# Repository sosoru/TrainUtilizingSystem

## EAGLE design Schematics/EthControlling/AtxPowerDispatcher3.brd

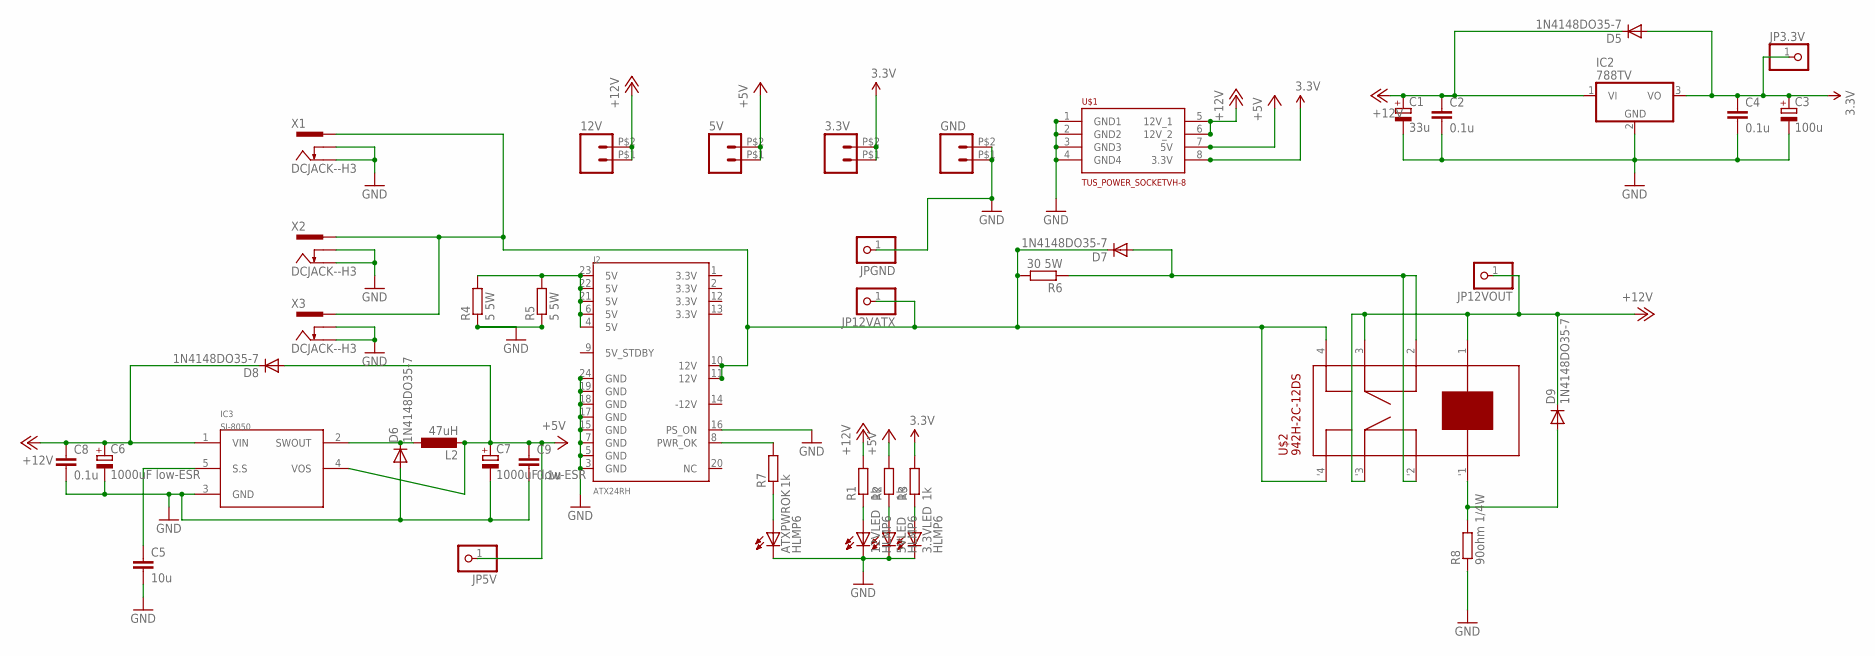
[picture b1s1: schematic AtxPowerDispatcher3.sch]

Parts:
3.3V, 5V, 12V: M02PTH2; 1X02_BIG
3.3VLED, 5VLED: HLMP6; MPN HLMP-6500
12VLED: HLMP6
ATXPWROK: HLMP6; MPN HLMP-6500
C1: 33u; E2,5-6E
C2, C4, C8, C9: 0.1u; C0603
C3: 100u; E2,5-6E
C5: 10u; C1206
C6, C7: 1000uF low-ESR; E2,5-6E
D5, D6, D7, D8, D9: 1N4148DO35-7; DO35-7
GND: M02PTH2; 1X02_BIG
IC2: 788TV; TO220V
IC3: SI-8050; TO220-5
J2: ATX24RH; ATX24_RIGHT_ANGLE
JP3.3V, JP5V, JP12VATX, JP12VOUT: PINHD-1X1; 1X01
JPGND: PINHD-1X1; 1X01
L2: 47uH; 2200-12.7
R1, R2, R3, R7: 1k; R0603
R4, R5: 5 5W; 0922/22
R6: 30 5W; 0922/22
R8: 90ohm 1/4W; 0207/10
U$1: TUS_POWER_SOCKETVH-8; VH_8
U$2: 942H-2C-12DS; 942H
X1, X2, X3: DCJACK--H3; 2DC-0005D100--H3

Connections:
3.3V: 3.3V.P$1 (1), 3.3V.P$2 (2), C3.+, C4.1, D5.A, IC2.3 (VO), JP3.3V.1, R3.2, U$1.8 (3.3V)
+5V: 5V.P$1 (1), 5V.P$2 (2), C7.+, C9.1, D8.A, IC3.4 (VOS), JP5V.1, L2.2, R2.2, U$1.7 (5V)
+12V: 12V.P$1 (1), 12V.P$2 (2), C1.+, C2.1, C6.+, C8.1, D5.C, D8.C, D9.C, IC2.1 (VI), IC3.1 (VIN), JP12VOUT.1, R1.2, U$1.5 (12V_1), U$1.6 (12V_2), U$2.1 (4), U$2.3 (2), U$2.'3 ('2)
GND: 3.3VLED.K, 5VLED.K, 12VLED.K, ATXPWROK.K, C1.-, C2.2, C3.-, C4.2, C5.2, C6.-, C7.-, C8.2, C9.2, D6.A, GND.P$1 (1), GND.P$2 (2), IC2.2 (GND), IC3.3 (GND), J2.3 (GND), J2.5 (GND), J2.7 (GND), J2.15 (GND), J2.16 (PS_ON), J2.17 (GND), J2.18 (GND), J2.19 (GND), J2.24 (GND), JPGND.1, R4.1, R5.1, R8.1, U$1.1 (GND1), U$1.2 (GND2), U$1.3 (GND3), U$1.4 (GND4), X1.2, X1.3, X2.2, X2.3, X3.2, X3.3
unnamed: 12VLED.A, R1.1
unnamed: J2.8 (PWR_OK), R7.2
unnamed: J2.4 (5V), J2.6 (5V), J2.21 (5V), J2.22 (5V), J2.23 (5V), R4.2, R5.2
unnamed: 5VLED.A, R2.1
unnamed: 3.3VLED.A, R3.1
unnamed: ATXPWROK.A, R7.1
unnamed: D9.A, R8.2, U$2.'1 ('4)
unnamed: D6.C, IC3.2 (SWOUT), L2.1
unnamed: D7.A, R6.1, U$2.2 (3), U$2.'2 ('3)
unnamed: D7.C, J2.10 (12V), J2.11 (12V), JP12VATX.1, R6.2, U$2.4 (1), U$2.'4 ('1), X1.1, X2.1, X3.1
unnamed: C5.1, IC3.5 (S.S)

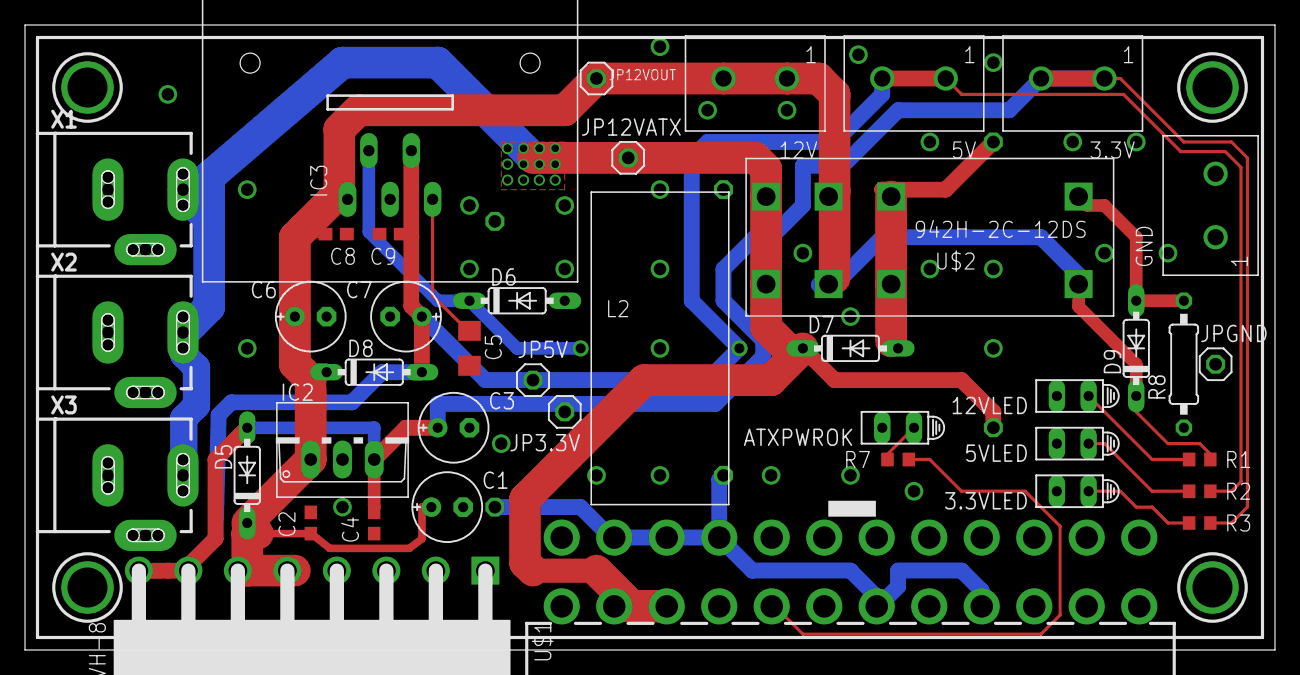
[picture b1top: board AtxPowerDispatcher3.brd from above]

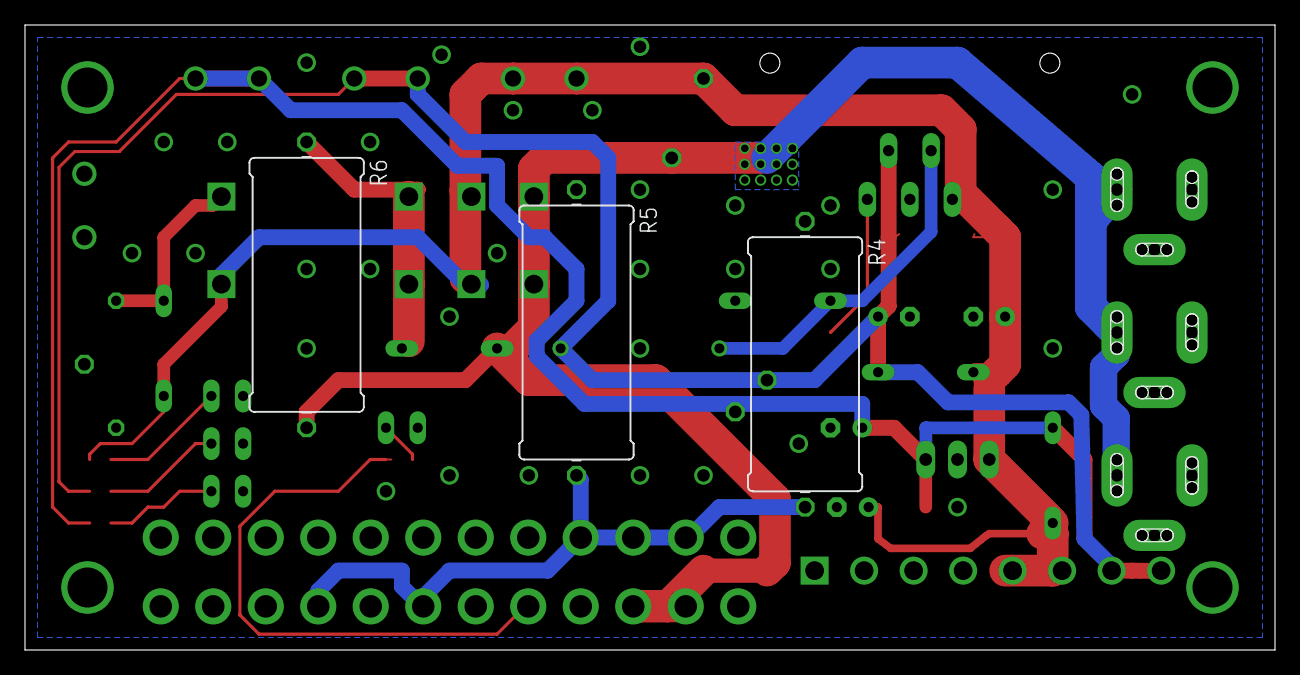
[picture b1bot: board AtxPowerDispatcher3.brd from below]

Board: 2 copper layers, 100.0 x 50.0 mm, 44 parts (3 on the bottom side), 15 nets.

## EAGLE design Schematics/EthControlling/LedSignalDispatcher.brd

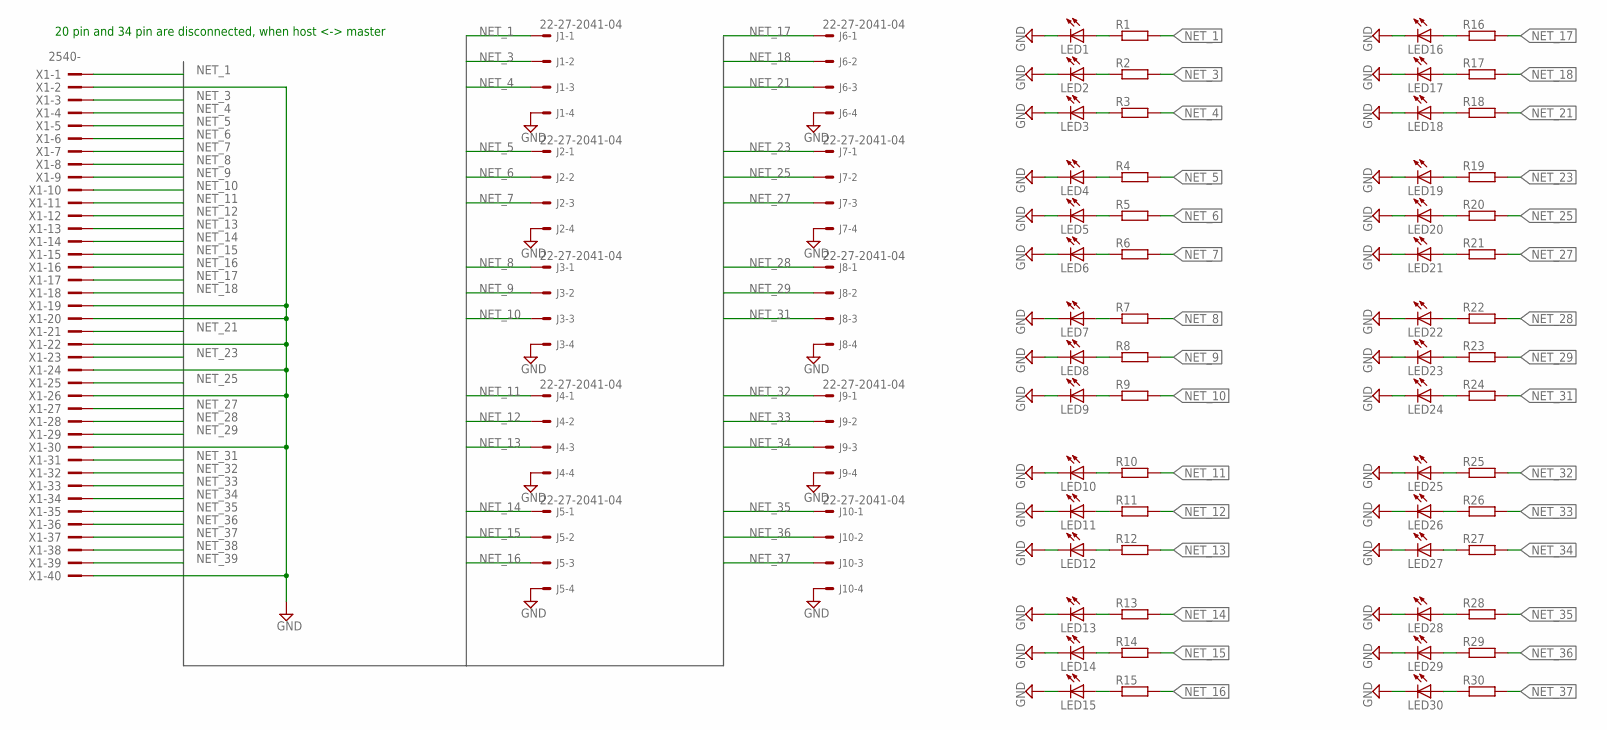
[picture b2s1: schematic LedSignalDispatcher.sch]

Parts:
J1, J2, J3, J4, J5, J6, J7, J8, J9, J10: 22-27-2041-04; 6410-04
LED1, LED2, LED3, LED4, LED5, LED6, LED7, LED8, LED9, LED10, LED11, LED12, LED13, LED14, LED15, LED16, LED17, LED18, LED19, LED20, LED21, LED22, LED23, LED24, LED25, LED26, LED27, LED28, LED29, LED30: LEDP-LCC-2; P-LCC-2
R1, R2, R3, R4, R5, R6, R7, R8, R9, R10, R11, R12, R13, R14, R15, R16, R17, R18, R19, R20, R21, R22, R23, R24, R25, R26, R27, R28, R29, R30: SMT-REF
X1: 2540-; PAK100/2500-40

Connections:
GND: J1.4, J2.4, J3.4, J4.4, J5.4, J6.4, J7.4, J8.4, J9.4, J10.4, LED1.C, LED2.C, LED3.C, LED4.C, LED5.C, LED6.C, LED7.C, LED8.C, LED9.C, LED10.C, LED11.C, LED12.C, LED13.C, LED14.C, LED15.C, LED16.C, LED17.C, LED18.C, LED19.C, LED20.C, LED21.C, LED22.C, LED23.C, LED24.C, LED25.C, LED26.C, LED27.C, LED28.C, LED29.C, LED30.C, X1.2, X1.19, X1.20, X1.22, X1.24, X1.26, X1.30, X1.40
unnamed: LED1.A, R1.2
unnamed: LED2.A, R2.2
unnamed: LED3.A, R3.2
unnamed: LED4.A, R4.2
unnamed: LED5.A, R5.2
unnamed: LED6.A, R6.2
unnamed: LED7.A, R7.2
unnamed: LED8.A, R8.2
unnamed: LED9.A, R9.2
unnamed: LED10.A, R10.2
unnamed: LED11.A, R11.2
unnamed: LED12.A, R12.2
unnamed: LED13.A, R13.2
unnamed: LED14.A, R14.2
unnamed: LED15.A, R15.2
unnamed: LED16.A, R16.2
unnamed: LED17.A, R17.2
unnamed: LED18.A, R18.2
unnamed: LED19.A, R19.2
unnamed: LED20.A, R20.2
unnamed: LED21.A, R21.2
unnamed: LED22.A, R22.2
unnamed: LED23.A, R23.2
unnamed: LED24.A, R24.2
unnamed: LED25.A, R25.2
unnamed: LED26.A, R26.2
unnamed: LED27.A, R27.2
unnamed: LED28.A, R28.2
unnamed: LED29.A, R29.2
unnamed: LED30.A, R30.2
NET_1: J1.1, R1.1, X1.1
NET_3: J1.2, R2.1, X1.3
NET_4: J1.3, R3.1, X1.4
NET_5: J2.1, R4.1, X1.5
NET_6: J2.2, R5.1, X1.6
NET_7: J2.3, R6.1, X1.7
NET_8: J3.1, R7.1, X1.8
NET_9: J3.2, R8.1, X1.9
NET_10: J3.3, R9.1, X1.10
NET_11: J4.1, R10.1, X1.11
NET_12: J4.2, R11.1, X1.12
NET_13: J4.3, R12.1, X1.13
NET_14: J5.1, R13.1, X1.14
NET_15: J5.2, R14.1, X1.15
NET_16: J5.3, R15.1, X1.16
NET_17: J6.1, R16.1, X1.17
NET_18: J6.2, R17.1, X1.18
NET_21: J6.3, R18.1, X1.21
NET_23: J7.1, R19.1, X1.23
NET_25: J7.2, R20.1, X1.25
NET_27: J7.3, R21.1, X1.27
NET_28: J8.1, R22.1, X1.28
NET_29: J8.2, R23.1, X1.29
NET_31: J8.3, R24.1, X1.31
NET_32: J9.1, R25.1, X1.32
NET_33: J9.2, R26.1, X1.33
NET_34: J9.3, R27.1, X1.34
NET_35: J10.1, R28.1, X1.35
NET_36: J10.2, R29.1, X1.36
NET_37: J10.3, R30.1, X1.37
NET_38: X1.38
NET_39: X1.39

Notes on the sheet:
20 pin and 34 pin are disconnected, when host <-> master

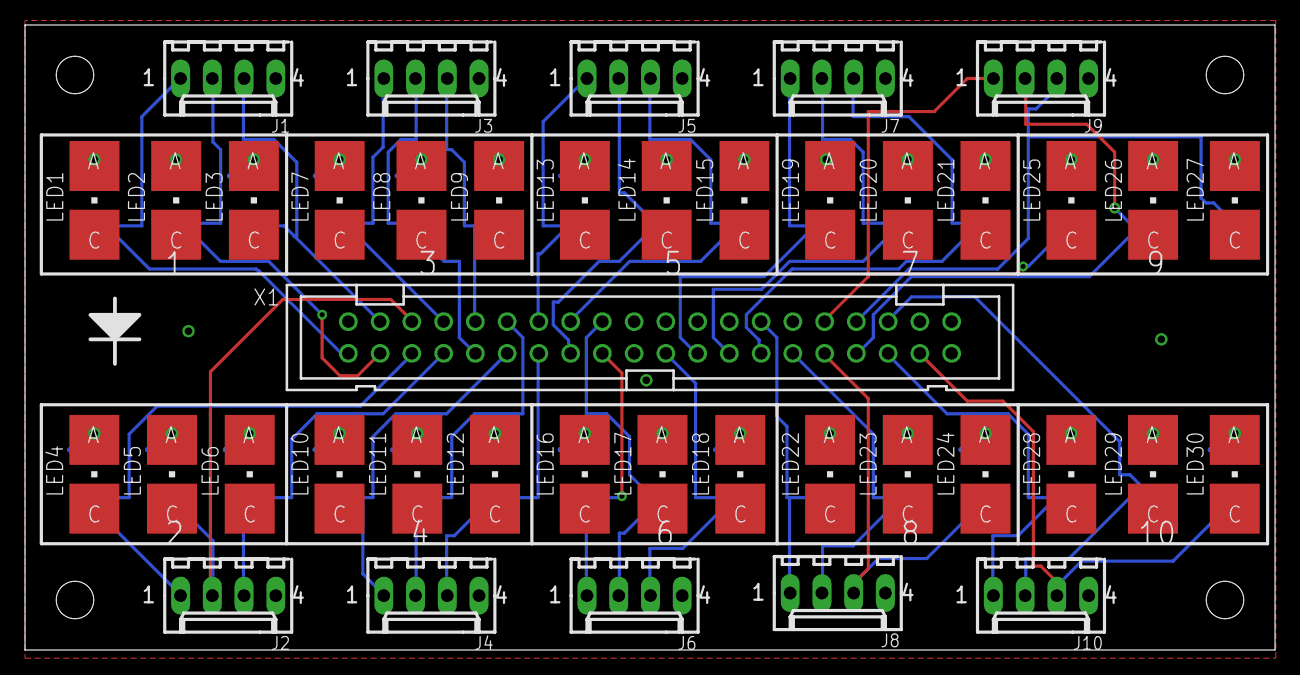
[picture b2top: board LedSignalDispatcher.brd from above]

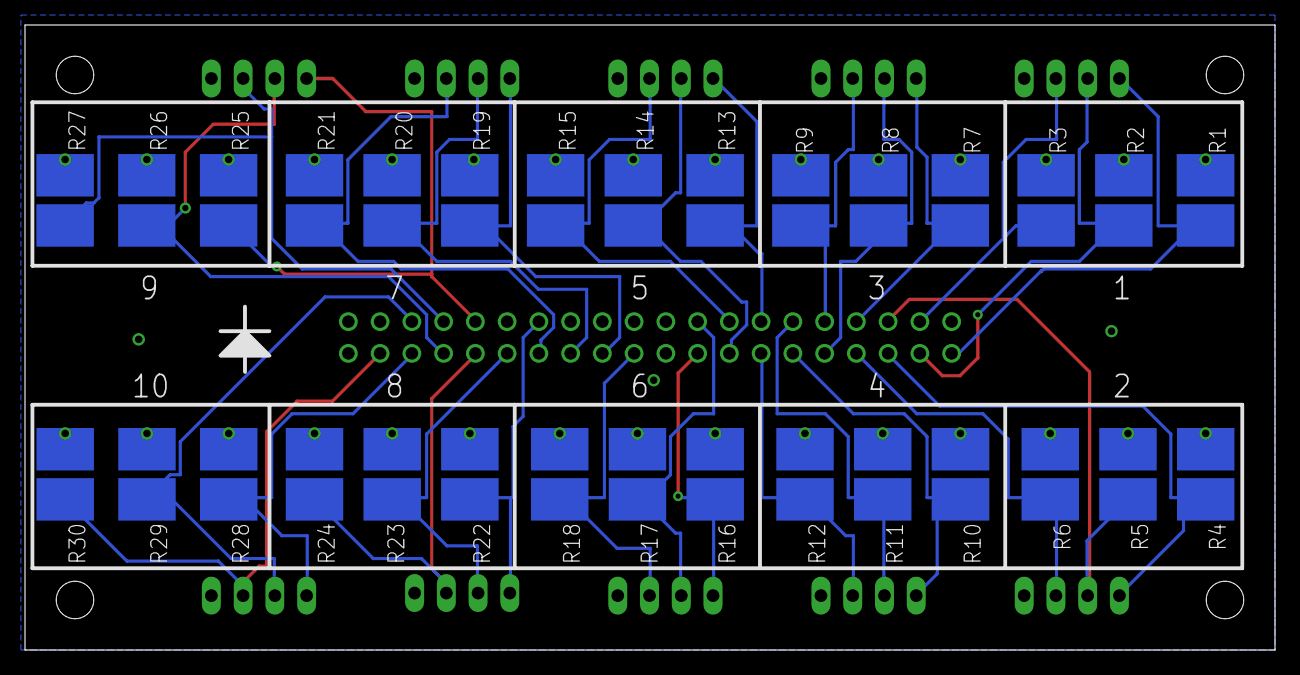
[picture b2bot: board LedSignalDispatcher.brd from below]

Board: 2 copper layers, 100.0 x 50.0 mm, 71 parts (30 on the bottom side), 61 nets.

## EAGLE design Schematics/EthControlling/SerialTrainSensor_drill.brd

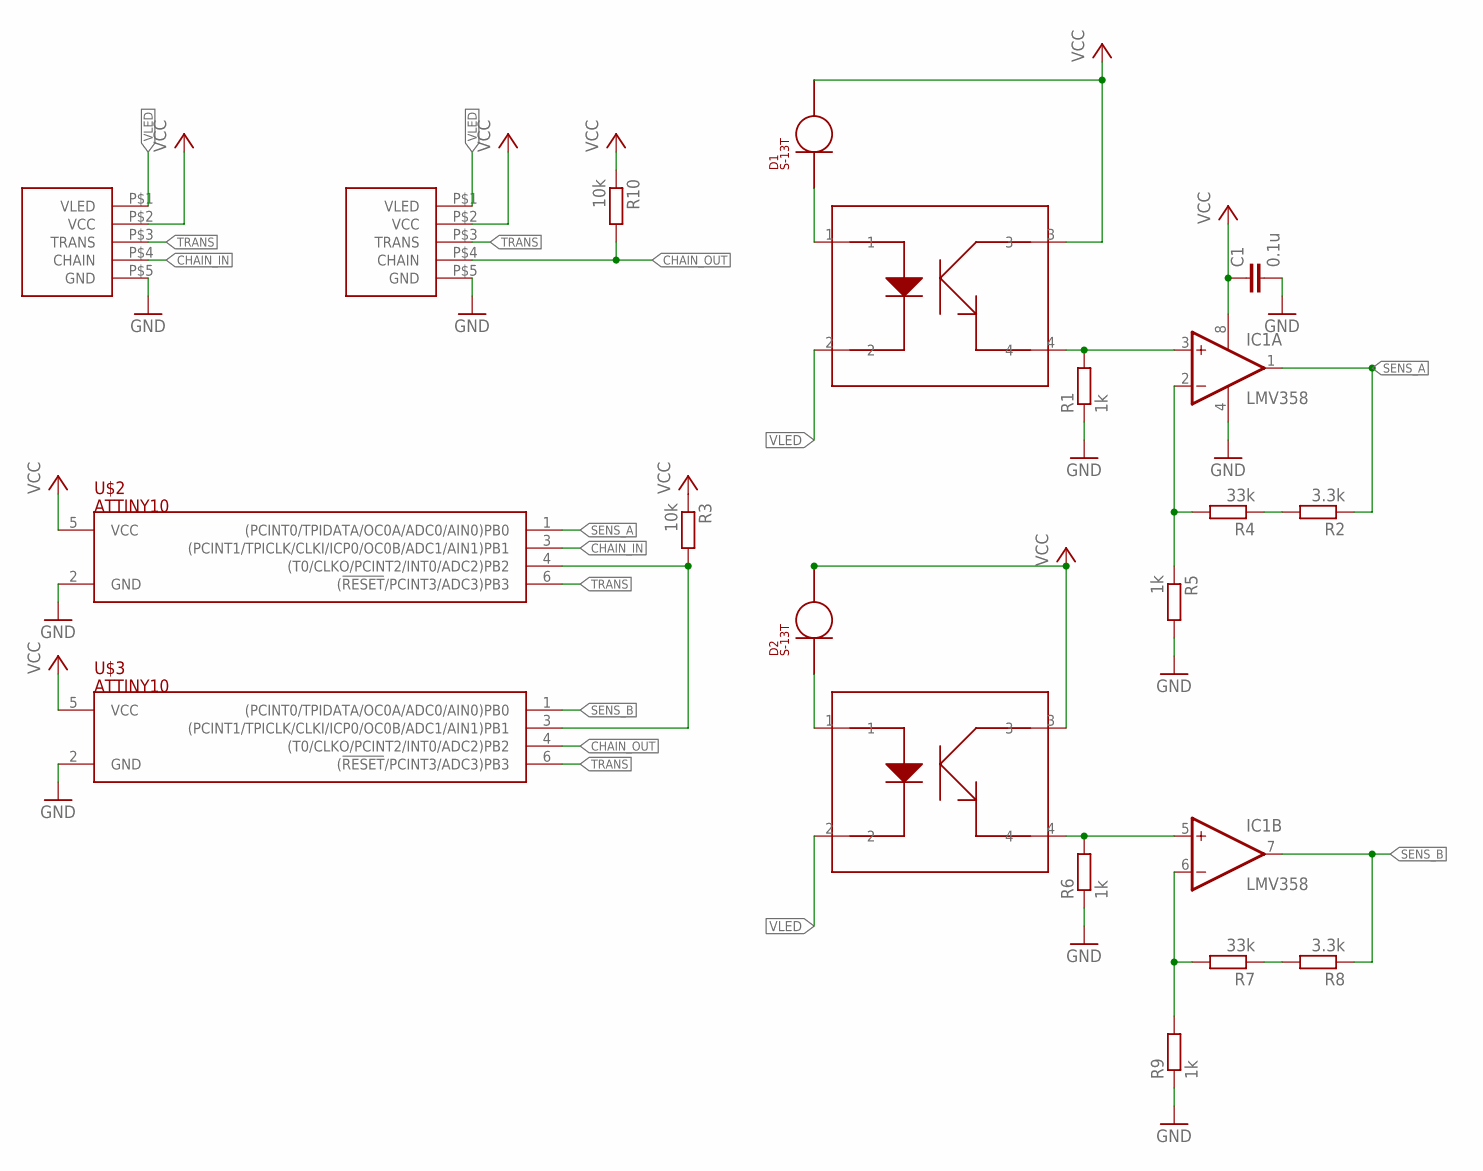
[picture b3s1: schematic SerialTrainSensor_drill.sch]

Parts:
C1: 0.1u; C0603
D1, D2: S-13T; S-1*3T
IC1: LMV358; TSSOP8
R1, R5, R6, R9: 1k; R0603
R2, R8: 3.3k; R0603
R3, R10: 10k; R0603
R4, R7: 33k; R0603
SMD1, SMD2: SERIAL_SENSORHALF; SERIAL_5_HALF
U$1, U$4: TPR-105F
U$2, U$3: ATTINY10; SOT-23

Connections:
CHAIN_IN: SMD1.P$4 (CHAIN), U$2.3 ((PCINT1/TPICLK/CLKI/ICP0/OC0B/ADC1/AIN1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)
CHAIN_OUT: R10.2, SMD2.P$4 (CHAIN), U$3.4 ((T0/CLKO/PCINT2/INT0/ADC2)PB2)
GND: C1.2, IC1.4 (V-), R1.1, R5.2, R6.1, R9.1, SMD1.P$5 (GND), SMD2.P$5 (GND), U$2.2 (GND), U$3.2 (GND)
unnamed: D1.C, U$1.1
unnamed: IC1.3 (+IN), R1.2, U$1.4
unnamed: D2.C, U$4.1
unnamed: R3.2, U$2.4 ((T0/CLKO/PCINT2/INT0/ADC2)PB2), U$3.3 ((PCINT1/TPICLK/CLKI/ICP0/OC0B/ADC1/AIN1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)
unnamed: IC1.5 (+IN), R6.2, U$4.4
unnamed: IC1.2 (-IN), R4.2, R5.1
unnamed: IC1.6 (-IN), R7.2, R9.2
unnamed: R2.2, R4.1
unnamed: R7.1, R8.2
SENS_A: IC1.1 (OUT), R2.1, U$2.1 ((PCINT0/TPIDATA/OC0A/ADC0/AIN0)PB0)
SENS_B: IC1.7 (OUT), R8.1, U$3.1 ((PCINT0/TPIDATA/OC0A/ADC0/AIN0)PB0)
TRANS: SMD1.P$3 (TRANS), SMD2.P$3 (TRANS), U$2.6 ((!RESET!/PCINT3/ADC3)PB3), U$3.6 ((!RESET!/PCINT3/ADC3)PB3)
VCC: C1.1, D1.A, D2.A, IC1.8 (V+), R3.1, R10.1, SMD1.P$2 (VCC), SMD2.P$2 (VCC), U$1.3, U$2.5 (VCC), U$3.5 (VCC), U$4.3
VLED: SMD1.P$1 (VLED), SMD2.P$1 (VLED), U$1.2, U$4.2

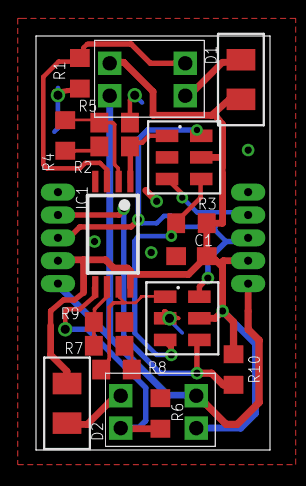
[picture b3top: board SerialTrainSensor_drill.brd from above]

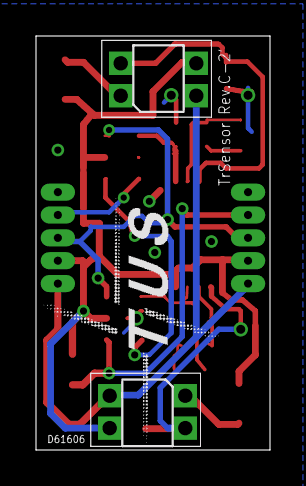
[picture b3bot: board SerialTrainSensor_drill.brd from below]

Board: 2 copper layers, 13.0 x 23.0 mm, 20 parts (2 on the bottom side), 17 nets.

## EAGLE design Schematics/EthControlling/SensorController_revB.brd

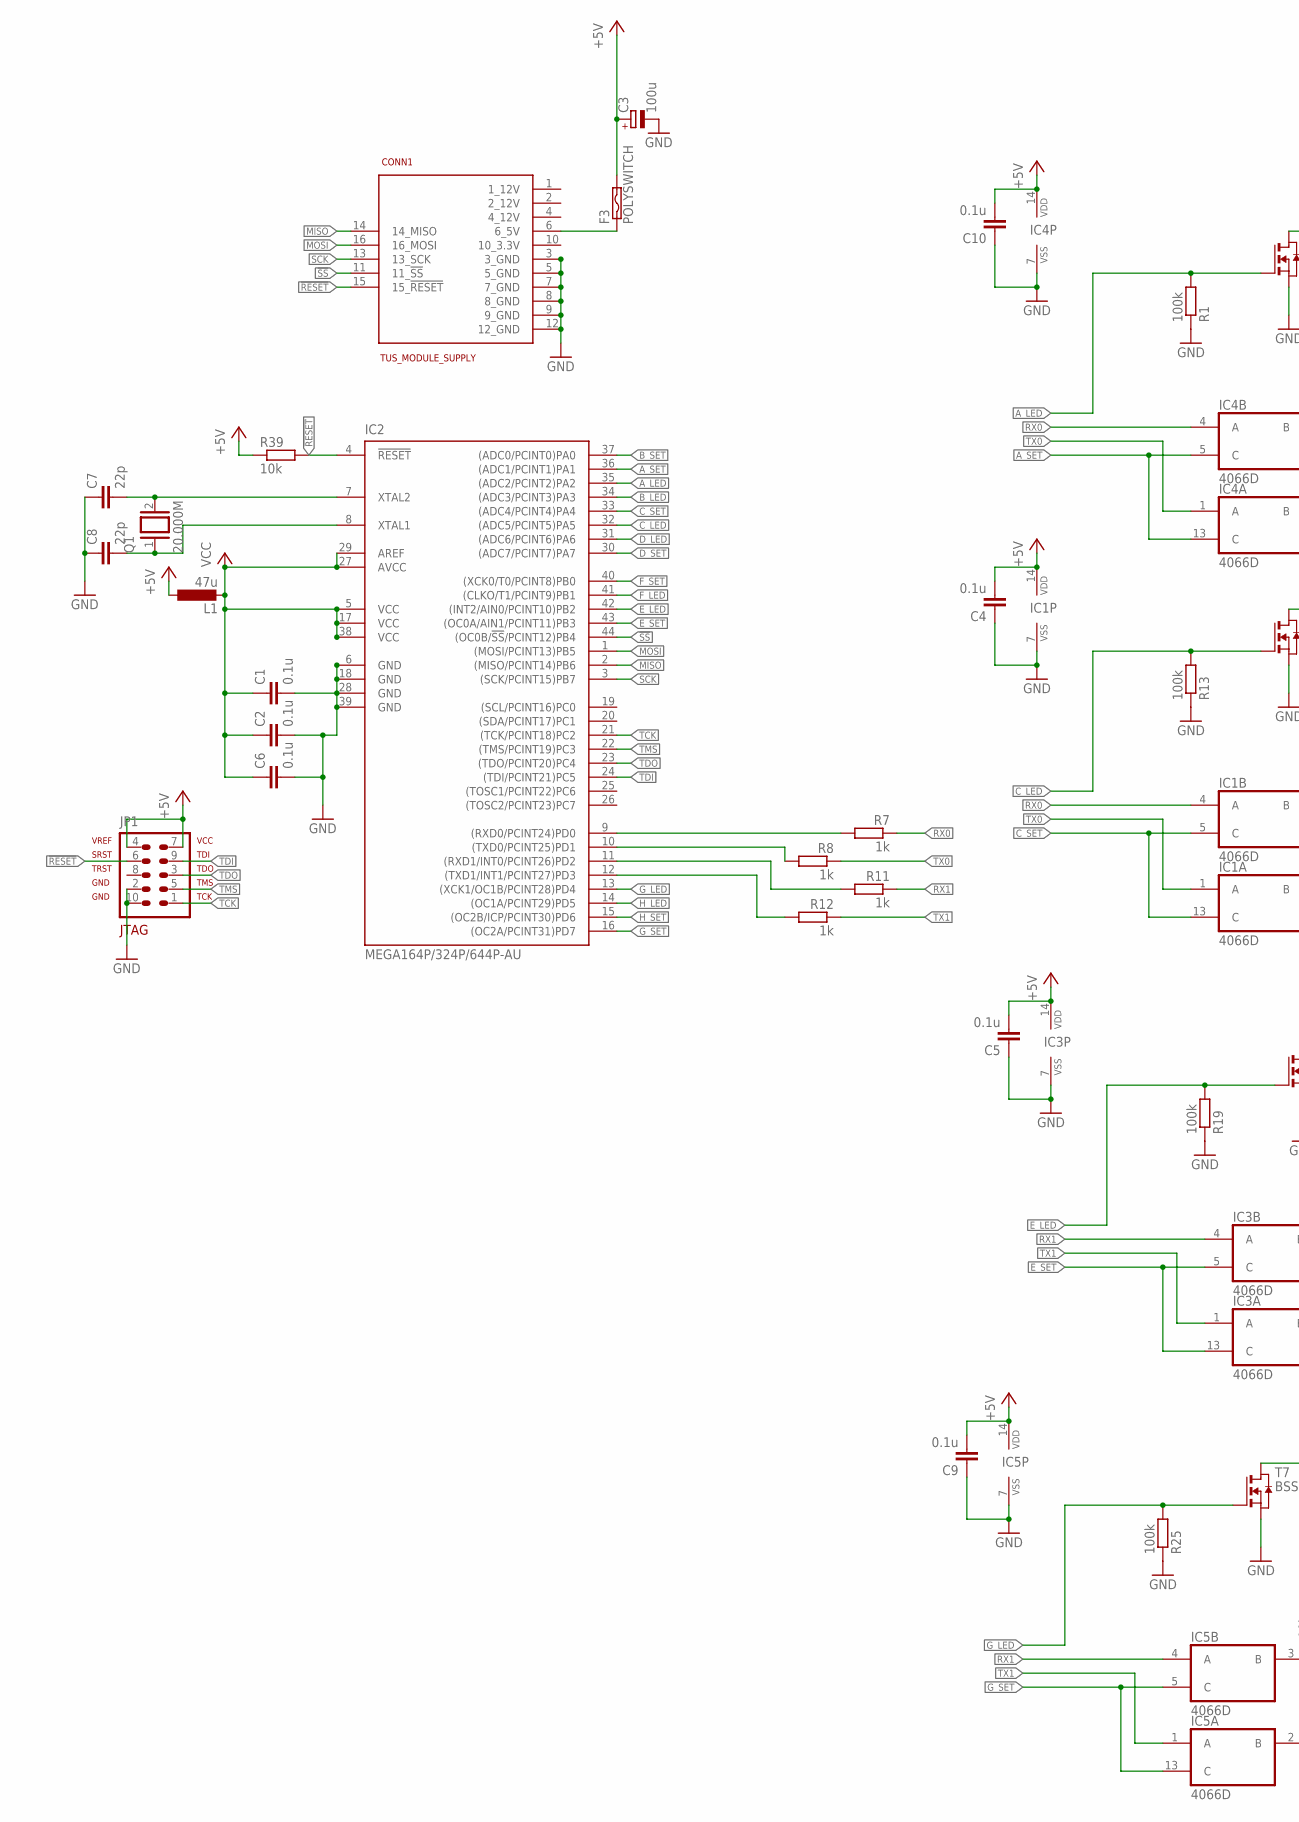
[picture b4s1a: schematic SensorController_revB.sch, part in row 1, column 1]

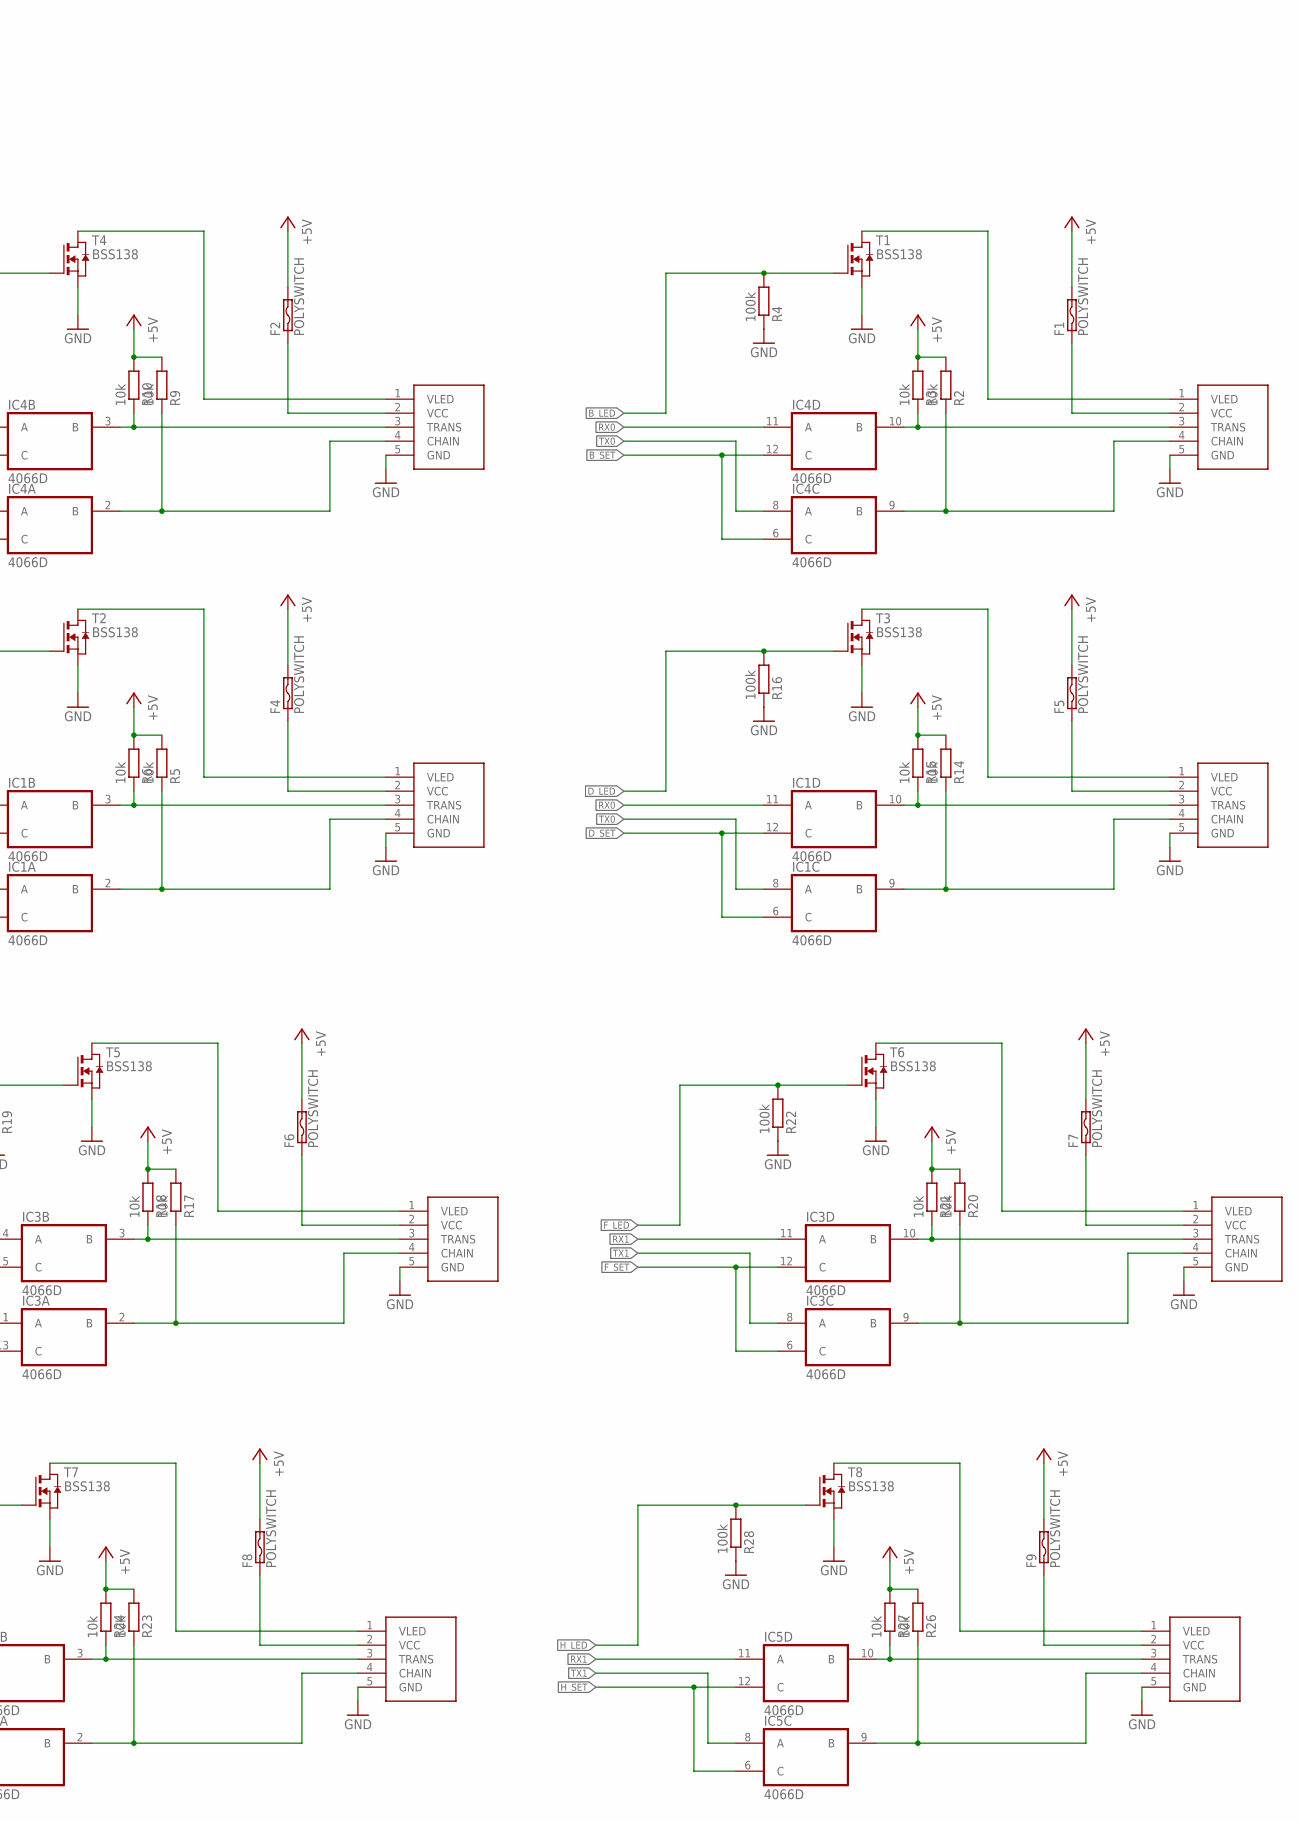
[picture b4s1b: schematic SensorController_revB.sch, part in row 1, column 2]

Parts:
A_OUT: SERIAL_SENSORXH; XH-5
B_OUT: SERIAL_SENSORXH; XH-5
C1, C2, C4, C5, C6, C9, C10: 0.1u; C1608
C3: 100u; E2,5-5
C7, C8: 22p; C1608
CONN1: TUS_MODULE_SUPPLY; 2X08
C_OUT: SERIAL_SENSORXH; XH-5
D_OUT: SERIAL_SENSORXH; XH-5
E_OUT: SERIAL_SENSORXH; XH-5
F1, F2, F3, F4, F5, F6, F7, F8, F9: POLYSWITCH; 0207/2V
F_OUT: SERIAL_SENSORXH; XH-5
G_OUT: SERIAL_SENSORXH; XH-5
H_OUT: SERIAL_SENSORXH; XH-5
IC1, IC3, IC4, IC5: 4066D; SO14
IC2: MEGA164P/324P/644P-AU; TQFP44
JP1: AVR-JTAG-10
L1: 47u; L1812
Q1: 20.000M; QS
R1, R4, R13, R16, R19, R22, R25, R28: 100k; R0603
R2, R3, R5, R6, R9, R10, R14, R15, R17, R18, R20, R21, R23, R24, R26, R27, R39: 10k; R0603
R7, R8, R11, R12: 1k; R0603
T1, T2, T3, T4, T5, T6, T7, T8: BSS138; SOT-23

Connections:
!RESET: CONN1.15 (15_!RESET), IC2.4 (!RESET), JP1.6, R39.2
!SS: CONN1.11 (11_!SS), IC2.44 ((OC0B/!SS!/PCINT12)PB4)
+5V: C3.+, C4.2, C5.2, C9.2, C10.2, F1.2, F2.2, F3.2, F4.2, F5.2, F6.2, F7.2, F8.2, F9.2, IC1.14 (VDD), IC3.14 (VDD), IC4.14 (VDD), IC5.14 (VDD), JP1.4, JP1.7, L1.1, R2.2, R3.2, R5.2, R6.2, R9.2, R10.2, R14.2, R15.2, R17.2, R18.2, R20.2, R21.2, R23.2, R24.2, R26.2, R27.2, R39.1
A_LED: IC2.35 ((ADC2/PCINT2)PA2), R1.2, T4.3 (G)
A_SET: IC2.36 ((ADC1/PCINT1)PA1), IC4.5 (C), IC4.13 (C)
B_LED: IC2.34 ((ADC3/PCINT3)PA3), R4.2, T1.3 (G)
B_SET: IC2.37 ((ADC0/PCINT0)PA0), IC4.6 (C), IC4.12 (C)
C_LED: IC2.32 ((ADC5/PCINT5)PA5), R13.2, T2.3 (G)
C_SET: IC1.5 (C), IC1.13 (C), IC2.33 ((ADC4/PCINT4)PA4)
D_LED: IC2.31 ((ADC6/PCINT6)PA6), R16.2, T3.3 (G)
D_SET: IC1.6 (C), IC1.12 (C), IC2.30 ((ADC7/PCINT7)PA7)
E_LED: IC2.42 ((INT2/AIN0/PCINT10)PB2), R19.2, T5.3 (G)
E_SET: IC2.43 ((OC0A/AIN1/PCINT11)PB3), IC3.5 (C), IC3.13 (C)
F_LED: IC2.41 ((CLKO/T1/PCINT9)PB1), R22.2, T6.3 (G)
F_SET: IC2.40 ((XCK0/T0/PCINT8)PB0), IC3.6 (C), IC3.12 (C)
GND: A_OUT.5 (GND), B_OUT.5 (GND), C1.2, C2.2, C3.-, C4.1, C5.1, C6.2, C7.1, C8.1, C9.1, C10.1, CONN1.3 (3_GND), CONN1.5 (5_GND), CONN1.7 (7_GND), CONN1.8 (8_GND), CONN1.9 (9_GND), CONN1.12 (12_GND), C_OUT.5 (GND), D_OUT.5 (GND), E_OUT.5 (GND), F_OUT.5 (GND), G_OUT.5 (GND), H_OUT.5 (GND), IC1.7 (VSS), IC2.6 (GND), IC2.18 (GND), IC2.28 (GND), IC2.39 (GND), IC3.7 (VSS), IC4.7 (VSS), IC5.7 (VSS), JP1.2, JP1.10, R1.1, R4.1, R13.1, R16.1, R19.1, R22.1, R25.1, R28.1, T1.2 (S), T2.2 (S), T3.2 (S), T4.2 (S), T5.2 (S), T6.2 (S), T7.2 (S), T8.2 (S)
G_LED: IC2.13 ((XCK1/OC1B/PCINT28)PD4), R25.2, T7.3 (G)
G_SET: IC2.16 ((OC2A/PCINT31)PD7), IC5.5 (C), IC5.13 (C)
H_LED: IC2.14 ((OC1A/PCINT29)PD5), R28.2, T8.3 (G)
H_SET: IC2.15 ((OC2B/ICP/PCINT30)PD6), IC5.6 (C), IC5.12 (C)
MISO: CONN1.14 (14_MISO), IC2.2 ((MISO/PCINT14)PB6)
MOSI: CONN1.16 (16_MOSI), IC2.1 ((MOSI/PCINT13)PB5)
unnamed: A_OUT.1 (VLED), T4.1 (D)
unnamed: C8.2, IC2.8 (XTAL1), Q1.1
unnamed: B_OUT.4 (CHAIN), IC4.9 (B), R2.1
unnamed: C7.2, IC2.7 (XTAL2), Q1.2
unnamed: B_OUT.3 (TRANS), IC4.10 (B), R3.1
unnamed: B_OUT.2 (VCC), F1.1
unnamed: B_OUT.1 (VLED), T1.1 (D)
unnamed: C_OUT.4 (CHAIN), IC1.2 (B), R5.1
unnamed: A_OUT.4 (CHAIN), IC4.2 (B), R9.1
unnamed: A_OUT.3 (TRANS), IC4.3 (B), R10.1
unnamed: C_OUT.3 (TRANS), IC1.3 (B), R6.1
unnamed: C_OUT.2 (VCC), F4.1
unnamed: C_OUT.1 (VLED), T2.1 (D)
unnamed: D_OUT.4 (CHAIN), IC1.9 (B), R14.1
unnamed: D_OUT.3 (TRANS), IC1.10 (B), R15.1
unnamed: D_OUT.2 (VCC), F5.1
unnamed: IC2.9 ((RXD0/PCINT24)PD0), R7.2
unnamed: A_OUT.2 (VCC), F2.1
unnamed: D_OUT.1 (VLED), T3.1 (D)
unnamed: IC2.10 ((TXD0/PCINT25)PD1), R8.2
unnamed: CONN1.6 (6_5V), F3.1
unnamed: IC2.11 ((RXD1/INT0/PCINT26)PD2), R11.2
unnamed: IC2.12 ((TXD1/INT1/PCINT27)PD3), R12.2
unnamed: E_OUT.4 (CHAIN), IC3.2 (B), R17.1
unnamed: E_OUT.3 (TRANS), IC3.3 (B), R18.1
unnamed: E_OUT.2 (VCC), F6.1
unnamed: E_OUT.1 (VLED), T5.1 (D)
unnamed: F_OUT.4 (CHAIN), IC3.9 (B), R20.1
unnamed: F_OUT.3 (TRANS), IC3.10 (B), R21.1
unnamed: F7.1, F_OUT.2 (VCC)
unnamed: F_OUT.1 (VLED), T6.1 (D)
unnamed: G_OUT.4 (CHAIN), IC5.2 (B), R23.1
unnamed: G_OUT.3 (TRANS), IC5.3 (B), R24.1
unnamed: F8.1, G_OUT.2 (VCC)
unnamed: G_OUT.1 (VLED), T7.1 (D)
unnamed: H_OUT.4 (CHAIN), IC5.9 (B), R26.1
unnamed: H_OUT.3 (TRANS), IC5.10 (B), R27.1
unnamed: F9.1, H_OUT.2 (VCC)
unnamed: H_OUT.1 (VLED), T8.1 (D)
RX0: IC1.4 (A), IC1.11 (A), IC4.4 (A), IC4.11 (A), R7.1
RX1: IC3.4 (A), IC3.11 (A), IC5.4 (A), IC5.11 (A), R11.1
SCK: CONN1.13 (13_SCK), IC2.3 ((SCK/PCINT15)PB7)
TCK: IC2.21 ((TCK/PCINT18)PC2), JP1.1
TDI: IC2.24 ((TDI/PCINT21)PC5), JP1.9
TDO: IC2.23 ((TDO/PCINT20)PC4), JP1.3
TMS: IC2.22 ((TMS/PCINT19)PC3), JP1.5
TX0: IC1.1 (A), IC1.8 (A), IC4.1 (A), IC4.8 (A), R8.1
TX1: IC3.1 (A), IC3.8 (A), IC5.1 (A), IC5.8 (A), R12.1
VCC: C1.1, C2.1, C6.1, IC2.5 (VCC), IC2.17 (VCC), IC2.27 (AVCC), IC2.29 (AREF), IC2.38 (VCC), L1.2

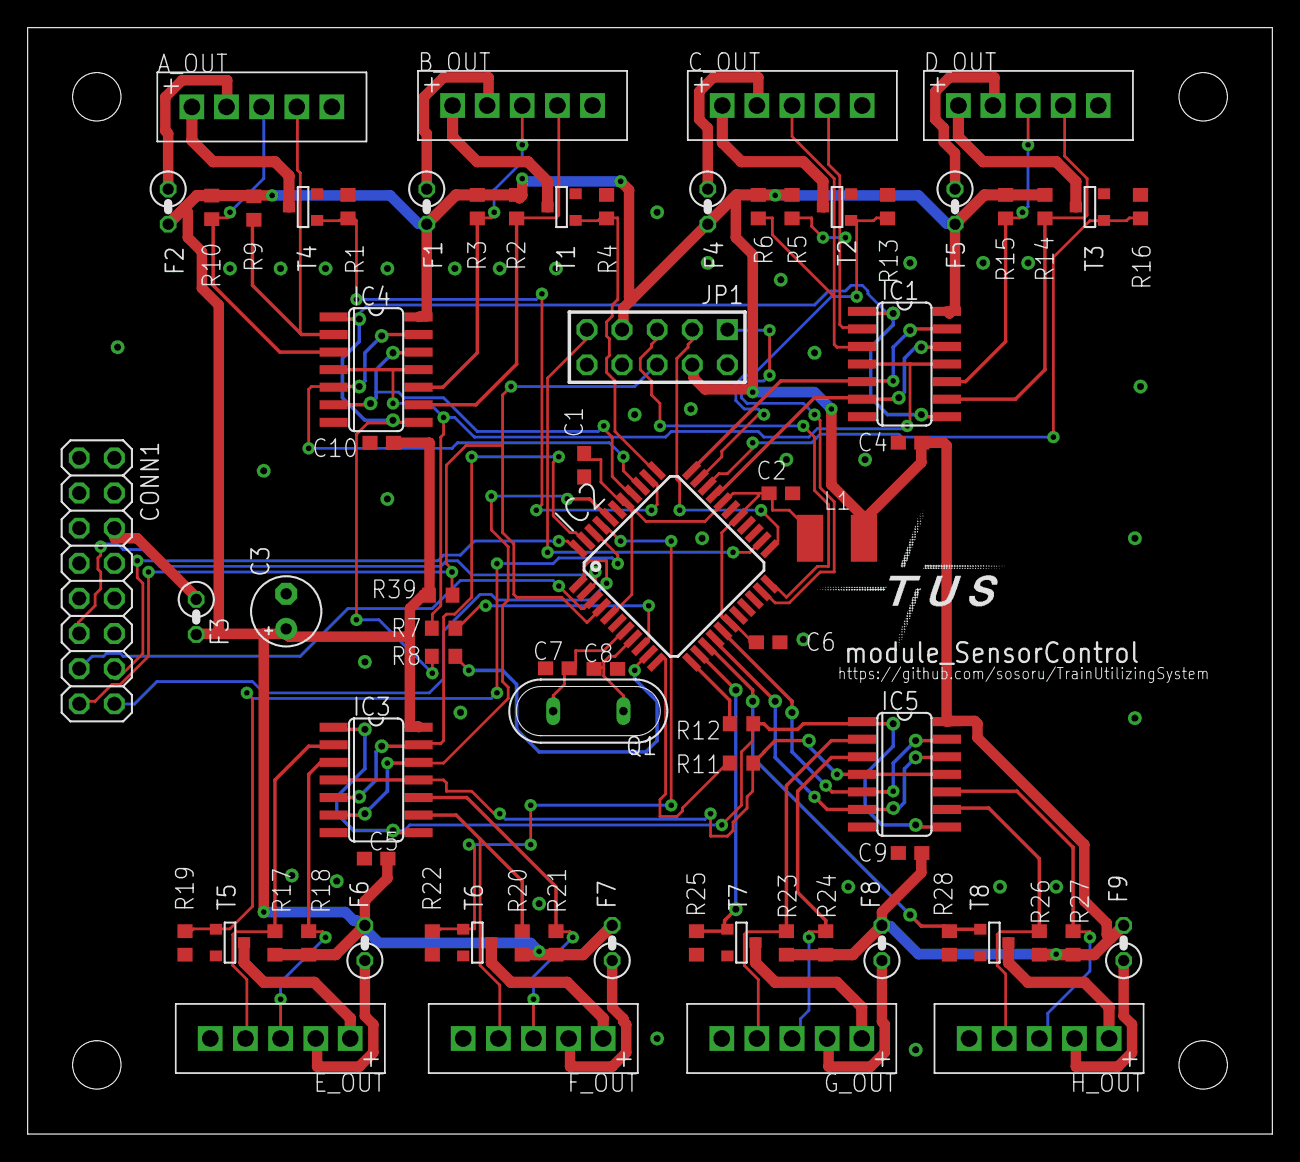
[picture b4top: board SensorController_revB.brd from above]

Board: 2 copper layers, 90.0 x 80.0 mm, 73 parts (0 on the bottom side), 71 nets.

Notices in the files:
parts and their libraries:
SparkFun: Licensing: CC v3.0 Share-Alike You are welcome to use this library for commercial purposes.
